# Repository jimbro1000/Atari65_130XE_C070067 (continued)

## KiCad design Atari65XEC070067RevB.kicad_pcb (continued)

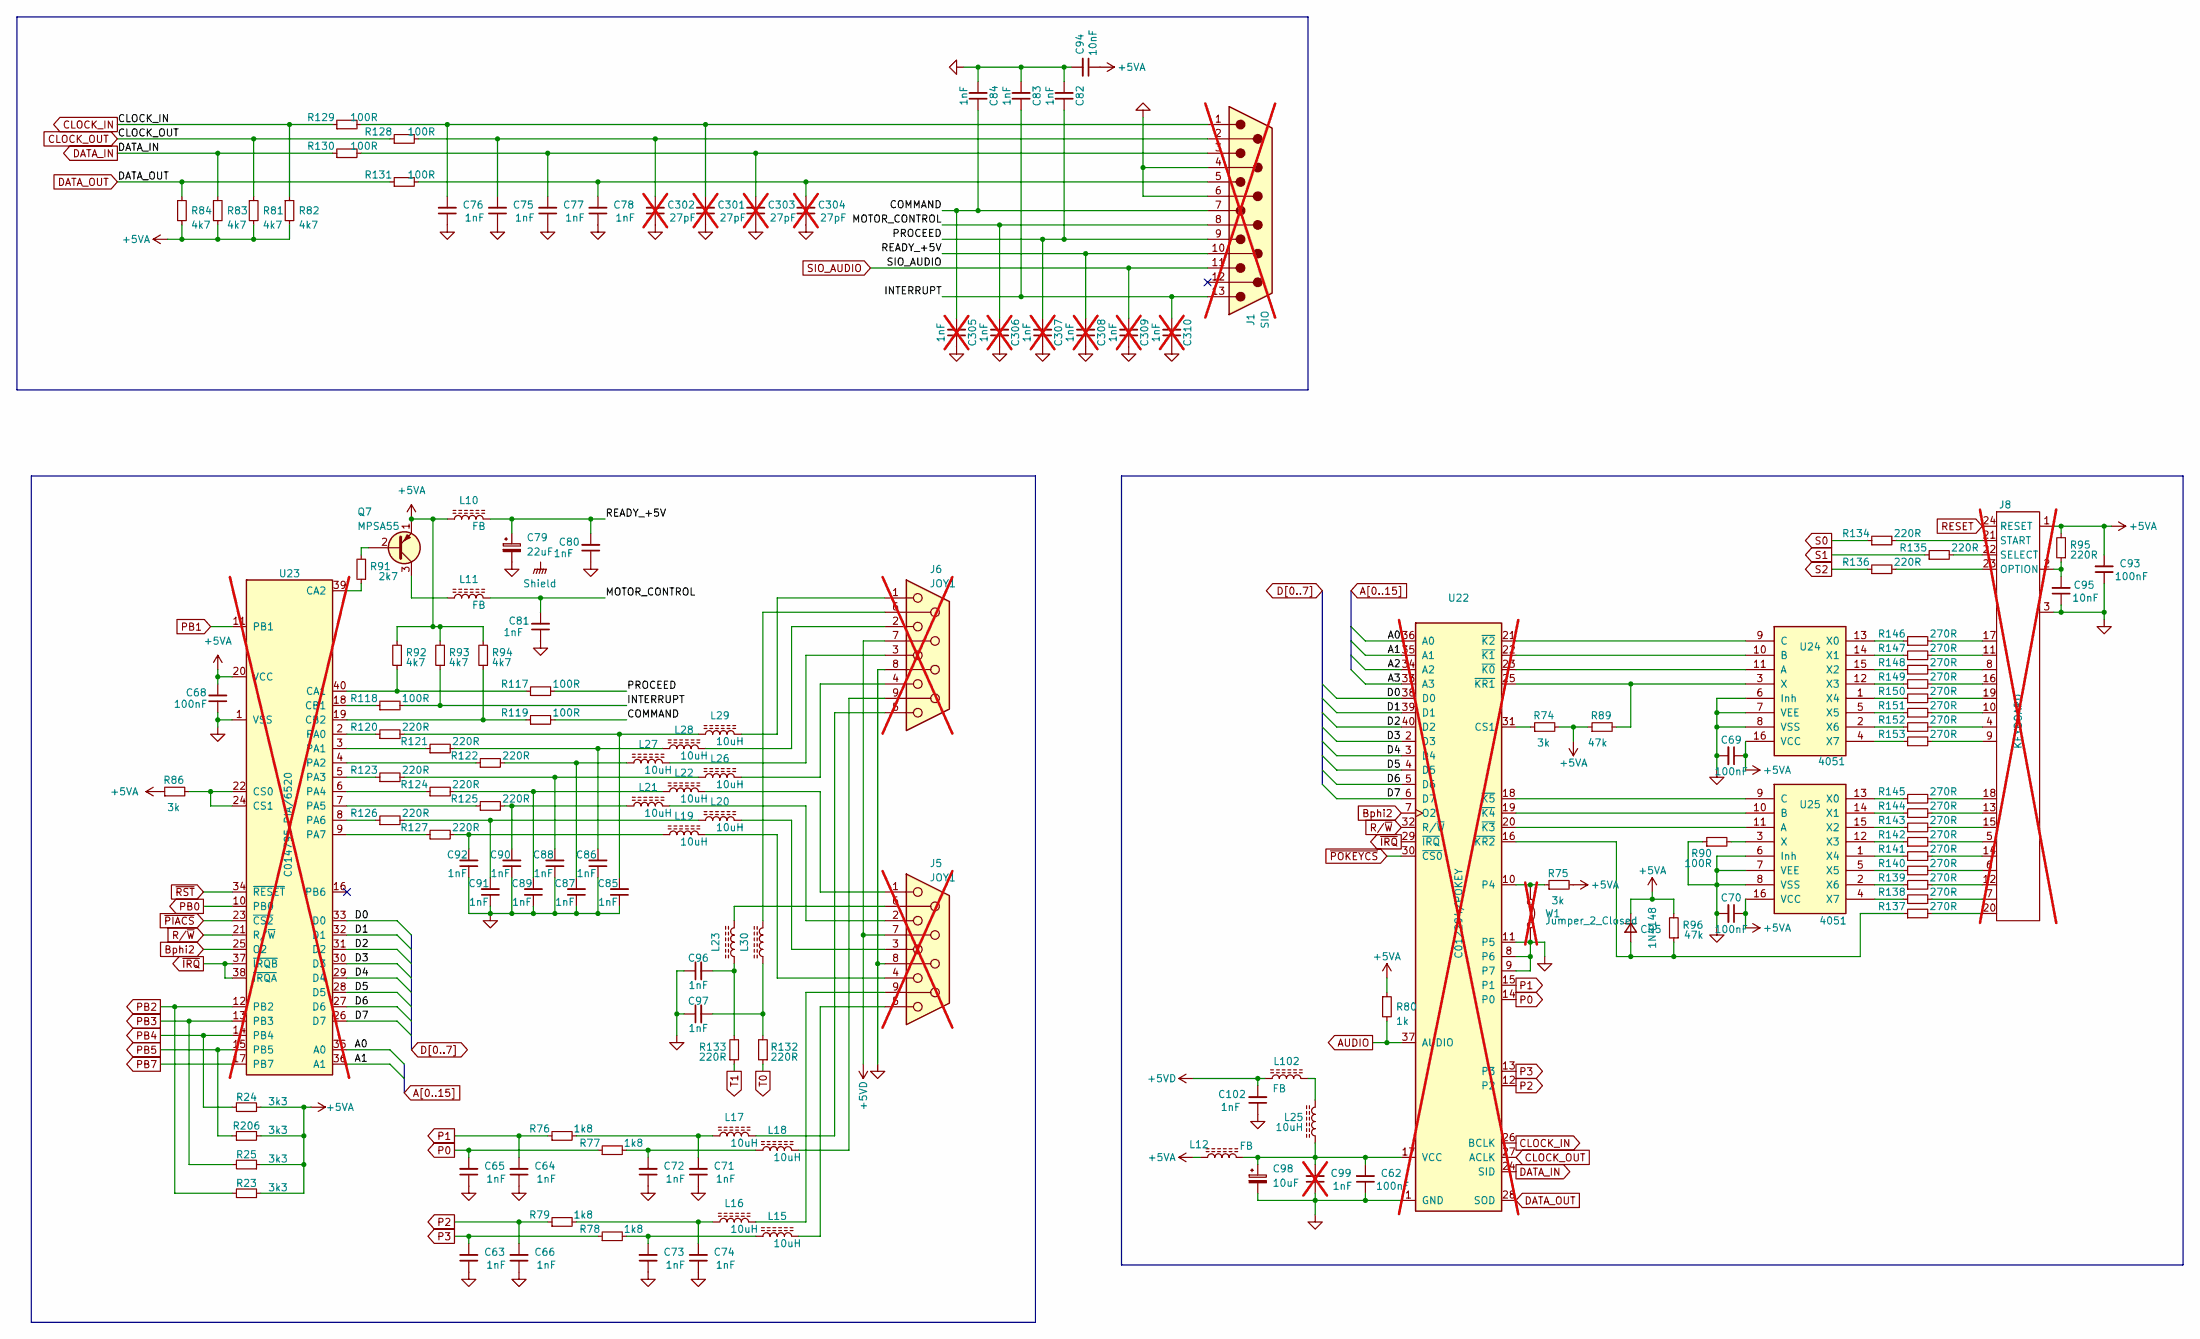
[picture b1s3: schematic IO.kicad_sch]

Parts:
C62, C68, C69, C70, C93: 100nF; C_Axial_L5.1mm_D2.7mm_P12.72mm_Horizontal; DigiKey 1109PHCT-ND
C63, C64, C65, C66, C71, C72, C73, C74, C75, C76, C77, C78, C80, C81, C82, C83, C84, C85, C86, C87, C88, C89, C90, C91, C92, C96, C97, C102: 1nF; C_Axial_L5.1mm_D2.7mm_P12.72mm_Horizontal; DigiKey 1216PHCT-ND
C79: 22uF; CP_Axial_L11.0mm_D5.0mm_P18.00mm_Horizontal; DigiKey 1572-1393-ND
C94, C95: 10nF; C_Axial_L5.1mm_D2.7mm_P12.72mm_Horizontal; DigiKey 1103PHCT-ND
C98: 10uF; CP_Axial_L11.0mm_D5.0mm_P18.00mm_Horizontal; DigiKey 1572-1035-1-ND
C99: 1nF; C_Axial_L5.1mm_D2.7mm_P12.72mm_Horizontal; DigiKey 1216PHCT-ND; not fitted
C301, C302, C303, C304: 27pF; C_Disc_D3.0mm_W1.6mm_P3.0mm; not fitted
C305, C306, C307, C308, C309, C310: 1nF; C_Disc_D3.0mm_W1.6mm_P3.0mm; not fitted
CR5: 1N4148; D_DO-35_SOD27_P12.70mm_Horizontal; DigiKey 1N4148FS-ND
J1: SIO; DSUB-13_Pins_Horizontal_P2.77x2.84mm_EdgePinOffset7.70mm_Ho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; not fitted
J5, J6: JOY1; DSUB-9_Pins_Horizontal_P2.77x2.54mm_Atari; not fitted
J8: KEYBOARD; not fitted
L10, L11, L12, L23, L30, L102: FB; L_Axial_L7.0mm_D3.3mm_P12.70mm_Horizontal_Fastron_MICC; DigiKey 1934-1417-1-ND
L15, L16, L17, L18, L19, L20, L21, L22, L25, L26, L27, L28, L29: 10uH; L_Axial_L7.0mm_D3.3mm_P12.70mm_Horizontal_Fastron_MICC; DigiKey 535-AICC-02-100K-TCT-ND
Q7: MPSA55; TO-92L_Inline_Wide; DigiKey PN2907ABUFS-ND
R23, R24, R25, R206: 3k3; R_Axial_L9.0mm_D2.7mm_P12.70mm_Horizontal; DigiKey CF14JT3K30CT-ND
R74, R75, R86: 3k; R_Axial_L9.0mm_D2.7mm_P12.70mm_Horizontal; DigiKey CF14JT3K00CT-ND
R76, R77, R78, R79: 1k8; R_Axial_L9.0mm_D2.7mm_P12.70mm_Horizontal; DigiKey CF14JT1K80CT-ND
R80: 1k; R_Axial_L9.0mm_D2.7mm_P12.70mm_Horizontal; DigiKey CF14JT1K00CT-ND
R81, R82, R83, R84, R92, R93, R94: 4k7; R_Axial_L9.0mm_D2.7mm_P12.70mm_Horizontal; DigiKey CF14JT4K70CT-ND
R89, R96: 47k; R_Axial_L9.0mm_D2.7mm_P12.70mm_Horizontal; DigiKey S47KQCT-ND
R90, R117, R118, R119, R128, R129, R130, R131: 100R; R_Axial_L9.0mm_D2.7mm_P12.70mm_Horizontal; DigiKey CF14JT100RCT-ND
R91: 2k7; R_Axial_L9.0mm_D2.7mm_P12.70mm_Horizontal; DigiKey CF14JT2K70CT-ND
R95, R120, R121, R122, R123, R124, R125, R126, R127, R132, R133, R134, R135, R136: 220R; R_Axial_L9.0mm_D2.7mm_P12.70mm_Horizontal; DigiKey CF14JT220RCT-ND
R137, R138, R139, R140, R141, R142, R143, R144, R145, R146, R147, R148, R149, R150, R151, R152, R153: 270R; R_Axial_L9.0mm_D2.7mm_P12.70mm_Horizontal; DigiKey CF14JT270RCT-ND
U22: C012294/POKEY; DIP-40_W15.24mm; not fitted
U23: C014795 PIA/6520; DIP-40_W15.24mm; not fitted
U24, U25: 4051; DIP-16_W7.62mm; DigiKey 296-2057-5-ND
W1: Jumper_2_Closed; R_Axial_DIN0309_L9.0mm_D3.2mm_P12.70mm_Horizontal; not fitted

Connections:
+5VA: C68.2, C69.1, C70.1, C93.2, C94.1, CR5.1 (K), J8.1, L10.1, L12.1, Q7.1 (E), R23.1, R24.1, R25.1, R74.2, R75.2, R80.1, R81.2, R82.2, R83.2, R84.2, R86.1, R89.1, R92.2, R93.2, R94.2, R95.2, R96.2, R206.2, U23.20 (VCC), U24.16 (VCC), U25.16 (VCC); also elsewhere on the board
+5VD: C102.2, J5.7, J6.7, L102.1
/IO/COMMAND: C84.1, C305.2, J1.7, R119.2
/IO/INTERRUPT: C83.1, C310.2, J1.13, R93.1, R118.2
/IO/MOTOR_CONTROL: C81.2, C306.2, J1.8, L11.2
/IO/PROCEED: C82.1, C307.2, J1.9, R117.2
/IO/READY_+5V: C79.1, C80.2, C308.2, J1.10, L10.2
A0: U22.36 (A0), U23.35 (A0); also elsewhere on the board
A1: U22.35 (A1), U23.36 (A1); also elsewhere on the board
A2: U22.34 (A2); also elsewhere on the board
A3: U22.33 (A3); also elsewhere on the board
AUDIO: R80.2, U22.37 (AUDIO); also elsewhere on the board
Bphi2: U22.7 (O2), U23.25 (O2); also elsewhere on the board
CLOCK_IN: R82.1, R129.1, U22.26 (BCLK)
CLOCK_OUT: R81.1, R128.1, U22.27 (ACLK)
D0: U22.38 (D0), U23.33 (D0); also elsewhere on the board
D1: U22.39 (D1), U23.32 (D1); also elsewhere on the board
D2: U22.40 (D2), U23.31 (D2); also elsewhere on the board
D3: U22.2 (D3), U23.30 (D3); also elsewhere on the board
D4: U22.3 (D4), U23.29 (D4); also elsewhere on the board
D5: U22.4 (D5), U23.28 (D5); also elsewhere on the board
D6: U22.5 (D6), U23.27 (D6); also elsewhere on the board
D7: U22.6 (D7), U23.26 (D7); also elsewhere on the board
DATA_IN: R83.1, R130.1, U22.24 (SID)
DATA_OUT: R84.1, R131.1, U22.28 (SOD)
GND: C62.1, C63.1, C64.1, C65.1, C66.1, C68.1, C69.2, C70.2, C71.1, C72.1, C73.1, C74.1, C75.1, C76.1, C77.1, C78.1, C79.2, C80.1, C81.1, C82.2, C83.2, C84.2, C85.1, C86.1, C87.1, C88.1, C89.1, C90.1, C91.1, C92.1, C93.1, C94.2, C95.1, C96.1, C97.1, C98.2, C99.1, C102.1, C301.1, C302.1, C303.1, C304.1, C305.1, C306.1, C307.1, C308.1, C309.1, C310.1, J1.4, J1.6, J5.8, J6.8, J8.3, R90.1, U22.1 (GND), U22.8 (P6), U22.9 (P7), U22.11 (P5), U23.1 (VSS), U24.6 (Inh), U24.7 (VEE), U24.8 (VSS), U25.6 (Inh), U25.7 (VEE), U25.8 (VSS), W1.2 (B); also elsewhere on the board
unnamed: C71.2, L17.1, R76.2
unnamed: C72.2, L18.1, R77.2
unnamed: C73.2, L15.1, R78.2
unnamed: C74.2, L16.1, R79.2
unnamed: C85.2, L29.1, R120.2
unnamed: C86.2, L28.1, R121.2
unnamed: C87.2, L27.1, R122.2
unnamed: C88.2, L26.1, R123.2
unnamed: C89.2, L22.1, R124.2
unnamed: C90.2, L21.1, R125.2
unnamed: C91.2, L20.1, R126.2
unnamed: C92.2, L19.1, R127.2
unnamed: C95.2, J8.2, R95.1
unnamed: C96.2, L23.1, R133.2
unnamed: C97.2, L30.1, R132.2
unnamed: C76.2, C301.2, J1.1, R129.2
unnamed: C75.2, C302.2, J1.2, R128.2
unnamed: C77.2, C303.2, J1.3, R130.2
unnamed: C78.2, C304.2, J1.5, R131.2
unnamed: CR5.2 (A), R96.1, R137.1, U22.16 (~KR2)
unnamed: J5.1, L22.2
unnamed: J5.2, L21.2
unnamed: J5.3, L20.2
unnamed: J5.4, L19.2
unnamed: J5.5, L15.2
unnamed: J5.6, L23.2
unnamed: J5.9, L16.2
unnamed: J6.1, L29.2
unnamed: J6.2, L28.2
unnamed: J6.3, L27.2
unnamed: J6.4, L26.2
unnamed: J6.5, L17.2
unnamed: J6.6, L30.2
unnamed: J6.9, L18.2
unnamed: J8.23 (OPTION), R136.2
unnamed: J8.4, R152.2
unnamed: J8.5, R142.2
unnamed: J8.6, R140.2
unnamed: J8.7, R138.2
unnamed: J8.8, R148.2
unnamed: J8.9, R153.2
unnamed: J8.10, R151.2
unnamed: J8.11, R147.2
unnamed: J8.12, R139.2
unnamed: J8.13, R144.2
unnamed: J8.14, R141.2
unnamed: J8.15, R143.2
unnamed: J8.16, R149.2
unnamed: J8.17, R146.2
unnamed: J8.18, R145.2
unnamed: J8.19, R150.2
unnamed: J8.20, R137.2
unnamed: J8.22 (SELECT), R135.2
unnamed: J8.21 (START), R134.2
unnamed: L25.2, L102.2
unnamed: Q7.2 (B), R91.2
unnamed: L11.1, Q7.3 (C)
unnamed: R74.1, U22.31 (CS1)
unnamed: R75.1, U22.10 (P4), W1.1 (A)
unnamed: C62.2, C98.1, C99.2, L12.2, L25.1, U22.17 (VCC)
unnamed: U22.23 (~K0), U24.11 (A)
unnamed: U22.22 (~K1), U24.10 (B)
unnamed: U22.21 (~K2), U24.9 (C)
unnamed: U22.20 (~K3), U25.11 (A)
unnamed: U22.19 (~K4), U25.10 (B)
unnamed: U22.18 (~K5), U25.9 (C)
unnamed: R89.2, U22.25 (~KR1), U24.3 (X)
unnamed: R92.1, R117.1, U23.40 (CA1)
unnamed: R91.1, U23.39 (CA2)
unnamed: R118.1, U23.18 (CB1)
unnamed: R94.1, R119.1, U23.19 (CB2)
unnamed: R86.2, U23.22 (CS0), U23.24 (CS1)
unnamed: R120.1, U23.2 (PA0)
unnamed: R121.1, U23.3 (PA1)
unnamed: R122.1, U23.4 (PA2)
unnamed: R123.1, U23.5 (PA3)
unnamed: R124.1, U23.6 (PA4)
unnamed: R125.1, U23.7 (PA5)
unnamed: R126.1, U23.8 (PA6)
unnamed: R127.1, U23.9 (PA7)
unnamed: R146.1, U24.13 (X0)
unnamed: R147.1, U24.14 (X1)
unnamed: R148.1, U24.15 (X2)
unnamed: R149.1, U24.12 (X3)
unnamed: R150.1, U24.1 (X4)
unnamed: R151.1, U24.5 (X5)
unnamed: R152.1, U24.2 (X6)
unnamed: R153.1, U24.4 (X7)
unnamed: R145.1, U25.13 (X0)
unnamed: R144.1, U25.14 (X1)
unnamed: R143.1, U25.15 (X2)
unnamed: R142.1, U25.12 (X3)
unnamed: R141.1, U25.1 (X4)
unnamed: R140.1, U25.5 (X5)
unnamed: R139.1, U25.2 (X6)
unnamed: R138.1, U25.4 (X7)
unnamed: R90.2, U25.3 (X)
P0: C65.2, R77.1, U22.14 (P0)
P1: C64.2, R76.1, U22.15 (P1)
P2: C66.2, R79.1, U22.12 (P2)
P3: C63.2, R78.1, U22.13 (P3)
PB0: U23.10 (PB0); also elsewhere on the board
PB1: U23.11 (PB1); also elsewhere on the board
PB2: R23.2, U23.12 (PB2); also elsewhere on the board
PB3: R25.2, U23.13 (PB3); also elsewhere on the board
PB4: R24.2, U23.14 (PB4); also elsewhere on the board
PB5: R206.1, U23.15 (PB5); also elsewhere on the board
PB7: U23.17 (PB7); also elsewhere on the board
RESET: J8.24 (RESET); also elsewhere on the board
R/~W: U22.32 (R/~W), U23.21 (R/~W); also elsewhere on the board
S0: R134.1; also elsewhere on the board
S1: R135.1; also elsewhere on the board
S2: R136.1; also elsewhere on the board
SIO_AUDIO: C309.2, J1.11; also elsewhere on the board
T0: R132.1; also elsewhere on the board
T1: R133.1; also elsewhere on the board
~IRQ: U22.29 (~IRQ), U23.37 (~IRQB), U23.38 (~IRQA); also elsewhere on the board
~PIACS: U23.23 (~CS2); also elsewhere on the board
~POKEYCS: U22.30 (~CS0); also elsewhere on the board
~RST: U23.34 (~RESET); also elsewhere on the board

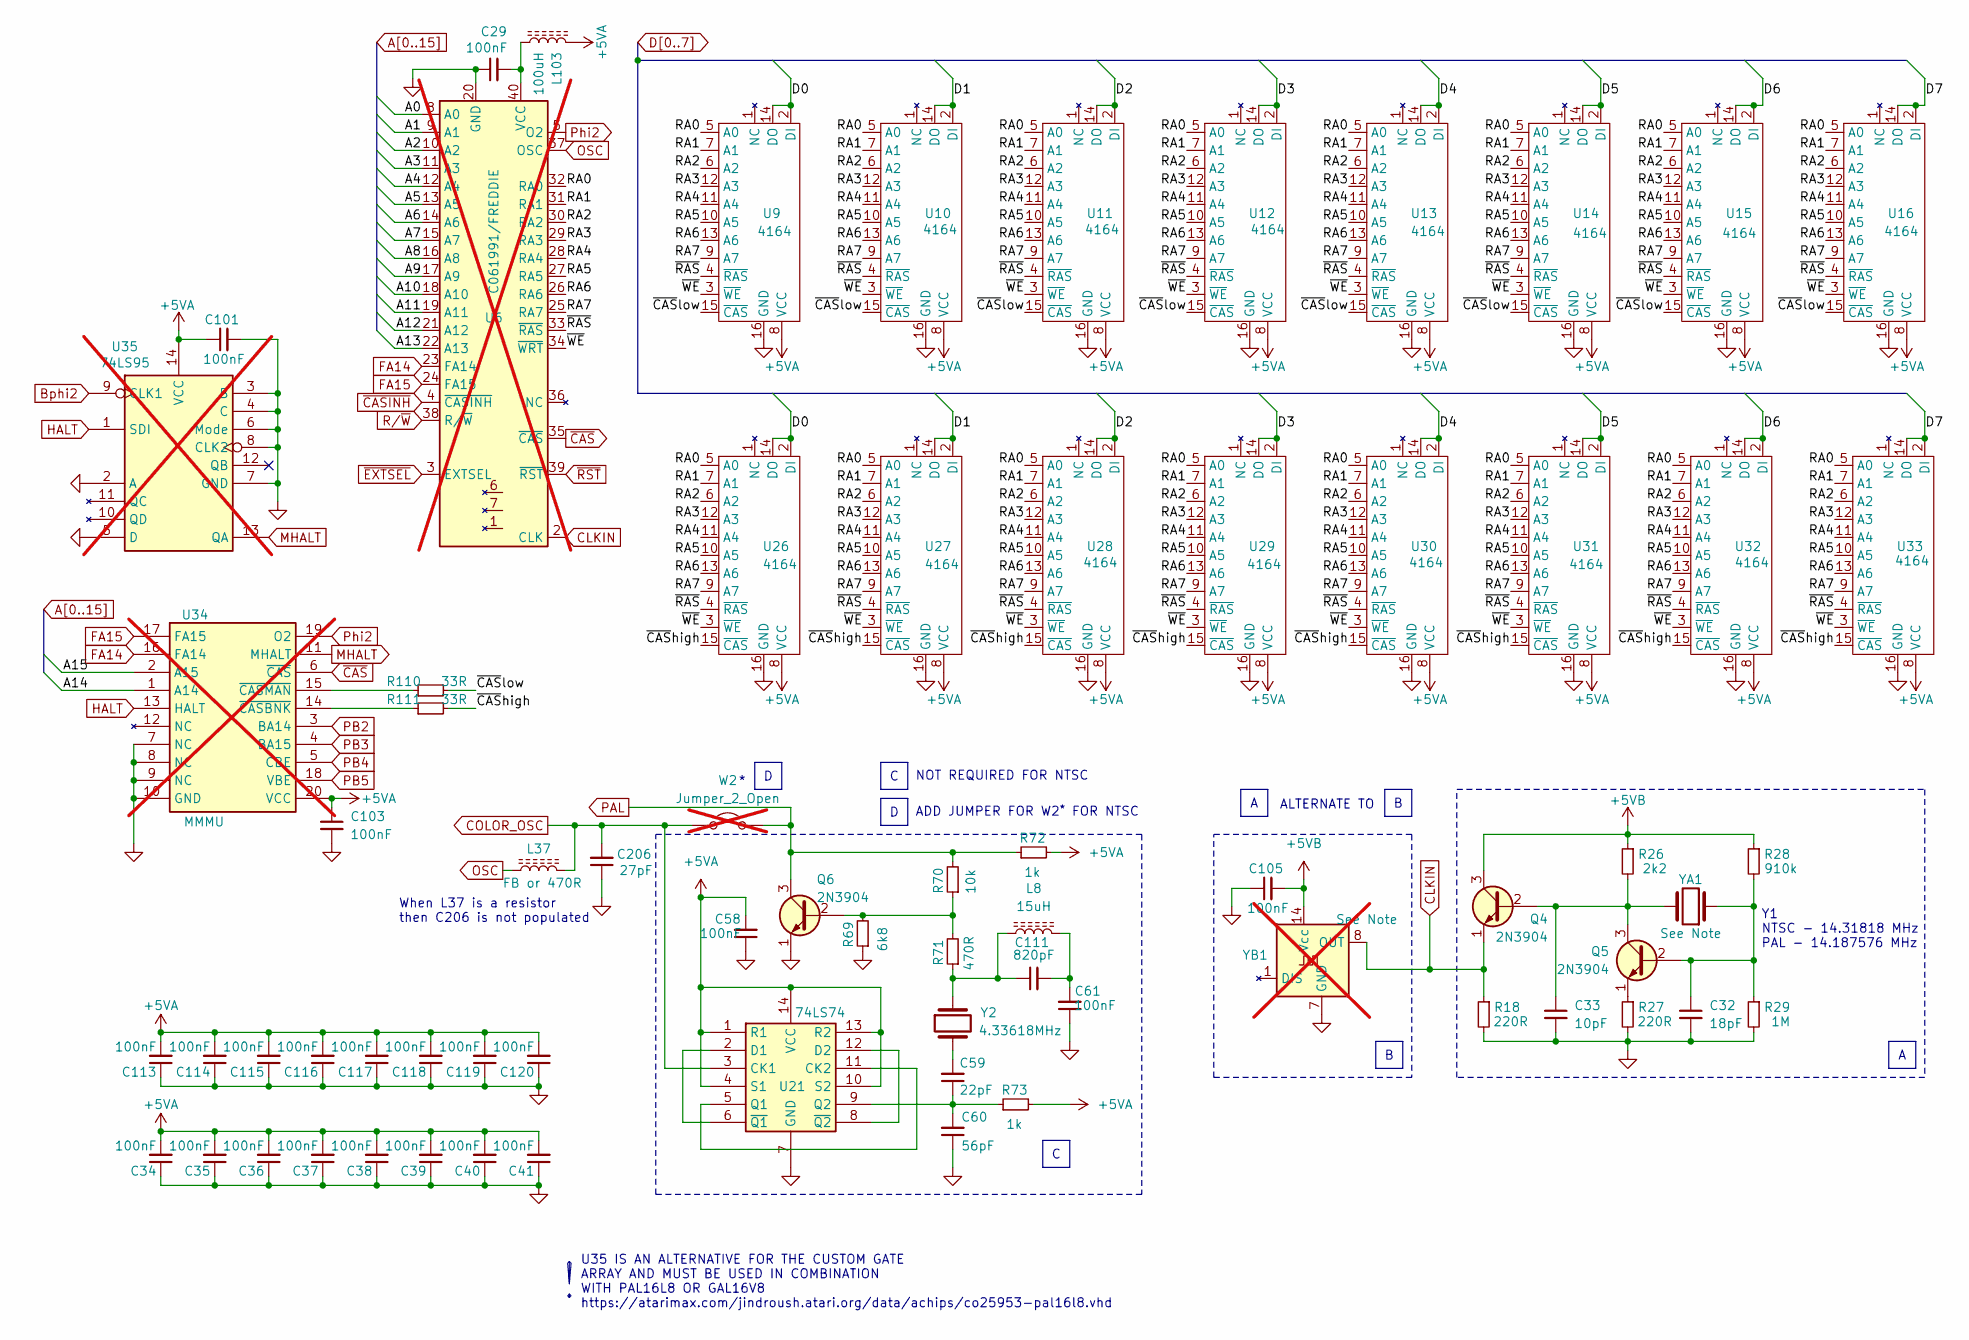
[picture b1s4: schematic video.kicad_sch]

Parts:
C29, C58, C61, C101, C103, C105: 100nF; C_Axial_L5.1mm_D2.7mm_P12.72mm_Horizontal; DigiKey 1109PHCT-ND
C32: 18pF; C_Axial_L5.1mm_D2.7mm_P12.72mm_Horizontal; DigiKey 1013PHCT-ND
C33: 10pF; C_Axial_L5.1mm_D2.7mm_P12.72mm_Horizontal; DigiKey 1011PHCT-ND
C34, C35, C36, C37, C38, C39, C40, C41, C113, C114, C115, C116, C117, C118, C119, C120: 100nF; C_Axial_L3.8mm_D2.6mm_P8.89mm_Horizontal; DigiKey 1109PHCT-ND
C59: 22pF; C_Axial_L5.1mm_D2.7mm_P12.72mm_Horizontal; DigiKey 1014PHCT-ND
C60: 56pF; C_Axial_L5.1mm_D2.7mm_P12.72mm_Horizontal; DigiKey 399-C410C510FAG5TA-ND
C111: 820pF; C_Axial_L5.1mm_D2.7mm_P12.72mm_Horizontal; DigiKey 399-C410C821K1R5TA-ND
C206: 27pF; C_Axial_L5.1mm_D2.7mm_P12.72mm_Horizontal; DigiKey 1015PHCT-ND
L8: 15uH; R_Axial_L9.0mm_D2.7mm_P12.70mm_Horizontal; DigiKey 78F150J-RC-ND
L37: FB or 470R; R_Axial_L9.0mm_D2.7mm_P12.70mm_Horizontal; DigiKey 1934-1417-1-ND
L103: 100uH; L_Axial_L7.0mm_D3.3mm_P12.70mm_Horizontal_Fastron_MICC; DigiKey 118-78F101J-TR-RCCT-ND
Q4, Q5, Q6: 2N3904; TO-92L_Inline_Wide; DigiKey 4878-2N3904CT-ND
R18, R27: 220R; R_Axial_L9.0mm_D2.7mm_P12.70mm_Horizontal; DigiKey CF14JT220RCT-ND
R26: 2k2; R_Axial_L9.0mm_D2.7mm_P12.70mm_Horizontal; DigiKey CF14JT2K20CT-ND
R28: 910k; R_Axial_L9.0mm_D2.7mm_P12.70mm_Horizontal; DigiKey CF14JT910KCT-ND
R29: 1M; R_Axial_L9.0mm_D2.7mm_P12.70mm_Horizontal; DigiKey CF14JT1M00CT-ND
R69: 6k8; R_Axial_L9.0mm_D2.7mm_P12.70mm_Horizontal; DigiKey CF14JT6K80CT-ND
R70: 10k; R_Axial_L9.0mm_D2.7mm_P12.70mm_Horizontal; DigiKey CF14JT10K0CT-ND
R71: 470R; R_Axial_L9.0mm_D2.7mm_P12.70mm_Horizontal; DigiKey CF14JT470RCT-ND
R72, R73: 1k; R_Axial_L9.0mm_D2.7mm_P12.70mm_Horizontal; DigiKey CF14JT1K00CT-ND
R110, R111: 33R; R_Axial_L9.0mm_D2.7mm_P12.70mm_Horizontal; DigiKey CF14JT33R0CT-ND
U6: C061991/FREDDIE; DIP-40_W15.24mm; not fitted
U9, U10, U11, U12, U13, U14, U15, U16, U26, U27, U28, U29, U30, U31, U32, U33: 4164; DIP-16_W7.62mm
U21: 74LS74; DIP-14_W7.62mm; DigiKey 296-1668-5-ND
U34: MMMU; DIP-20_W7.62mm; not fitted
U35: 74LS95; DIP-14_W7.62mm; not fitted
W2: Jumper_2_Open; R_Axial_DIN0309_L9.0mm_D3.2mm_P12.70mm_Horizontal; not fitted
Y2: 4.33618MHz; Crystal_HC49-U_Horizontal; DigiKey X1013-ND
YA1: See Note; Crystal_HC49-U_Horizontal; DigiKey 535-AB-14.31818MHZ-B2CT-ND
YB1: See Note; Oscillator_DIP-14; DigiKey X946-ND; not fitted

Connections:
+5VA: C34.2, C35.2, C36.2, C37.2, C38.2, C39.2, C40.2, C41.2, C58.2, C101.1, C103.1, C113.2, C114.2, C115.2, C116.2, C117.2, C118.2, C119.2, C120.2, L103.2, R72.2, R73.2, U9.8 (VCC), U10.8 (VCC), U11.8 (VCC), U12.8 (VCC), U13.8 (VCC), U14.8 (VCC), U15.8 (VCC), U16.8 (VCC), U21.1 (R1), U21.4 (S1), U21.10 (S2), U21.13 (R2), U21.14 (VCC), U26.8 (VCC), U27.8 (VCC), U28.8 (VCC), U29.8 (VCC), U30.8 (VCC), U31.8 (VCC), U32.8 (VCC), U33.8 (VCC), U34.20 (VCC), U35.14 (VCC); also elsewhere on the board
+5VB: C105.2, Q4.3 (C), R26.1, R28.1, YB1.14 (Vcc); also elsewhere on the board
/clocks+ram/RA0: U6.32 (RA0), U9.5 (A0), U10.5 (A0), U11.5 (A0), U12.5 (A0), U13.5 (A0), U14.5 (A0), U15.5 (A0), U16.5 (A0), U26.5 (A0), U27.5 (A0), U28.5 (A0), U29.5 (A0), U30.5 (A0), U31.5 (A0), U32.5 (A0), U33.5 (A0)
/clocks+ram/RA1: U6.31 (RA1), U9.7 (A1), U10.7 (A1), U11.7 (A1), U12.7 (A1), U13.7 (A1), U14.7 (A1), U15.7 (A1), U16.7 (A1), U26.7 (A1), U27.7 (A1), U28.7 (A1), U29.7 (A1), U30.7 (A1), U31.7 (A1), U32.7 (A1), U33.7 (A1)
/clocks+ram/RA2: U6.30 (RA2), U9.6 (A2), U10.6 (A2), U11.6 (A2), U12.6 (A2), U13.6 (A2), U14.6 (A2), U15.6 (A2), U16.6 (A2), U26.6 (A2), U27.6 (A2), U28.6 (A2), U29.6 (A2), U30.6 (A2), U31.6 (A2), U32.6 (A2), U33.6 (A2)
/clocks+ram/RA3: U6.29 (RA3), U9.12 (A3), U10.12 (A3), U11.12 (A3), U12.12 (A3), U13.12 (A3), U14.12 (A3), U15.12 (A3), U16.12 (A3), U26.12 (A3), U27.12 (A3), U28.12 (A3), U29.12 (A3), U30.12 (A3), U31.12 (A3), U32.12 (A3), U33.12 (A3)
/clocks+ram/RA4: U6.28 (RA4), U9.11 (A4), U10.11 (A4), U11.11 (A4), U12.11 (A4), U13.11 (A4), U14.11 (A4), U15.11 (A4), U16.11 (A4), U26.11 (A4), U27.11 (A4), U28.11 (A4), U29.11 (A4), U30.11 (A4), U31.11 (A4), U32.11 (A4), U33.11 (A4)
/clocks+ram/RA5: U6.27 (RA5), U9.10 (A5), U10.10 (A5), U11.10 (A5), U12.10 (A5), U13.10 (A5), U14.10 (A5), U15.10 (A5), U16.10 (A5), U26.10 (A5), U27.10 (A5), U28.10 (A5), U29.10 (A5), U30.10 (A5), U31.10 (A5), U32.10 (A5), U33.10 (A5)
/clocks+ram/RA6: U6.26 (RA6), U9.13 (A6), U10.13 (A6), U11.13 (A6), U12.13 (A6), U13.13 (A6), U14.13 (A6), U15.13 (A6), U16.13 (A6), U26.13 (A6), U27.13 (A6), U28.13 (A6), U29.13 (A6), U30.13 (A6), U31.13 (A6), U32.13 (A6), U33.13 (A6)
/clocks+ram/RA7: U6.25 (RA7), U9.9 (A7), U10.9 (A7), U11.9 (A7), U12.9 (A7), U13.9 (A7), U14.9 (A7), U15.9 (A7), U16.9 (A7), U26.9 (A7), U27.9 (A7), U28.9 (A7), U29.9 (A7), U30.9 (A7), U31.9 (A7), U32.9 (A7), U33.9 (A7)
/clocks+ram/~CAShigh: R111.2, U26.15 (~CAS), U27.15 (~CAS), U28.15 (~CAS), U29.15 (~CAS), U30.15 (~CAS), U31.15 (~CAS), U32.15 (~CAS), U33.15 (~CAS)
/clocks+ram/~CASlow: R110.2, U9.15 (~CAS), U10.15 (~CAS), U11.15 (~CAS), U12.15 (~CAS), U13.15 (~CAS), U14.15 (~CAS), U15.15 (~CAS), U16.15 (~CAS)
/clocks+ram/~RAS: U6.33 (~RAS), U9.4 (~RAS), U10.4 (~RAS), U11.4 (~RAS), U12.4 (~RAS), U13.4 (~RAS), U14.4 (~RAS), U15.4 (~RAS), U16.4 (~RAS), U26.4 (~RAS), U27.4 (~RAS), U28.4 (~RAS), U29.4 (~RAS), U30.4 (~RAS), U31.4 (~RAS), U32.4 (~RAS), U33.4 (~RAS)
/clocks+ram/~WE: U6.34 (~WRT), U9.3 (~WE), U10.3 (~WE), U11.3 (~WE), U12.3 (~WE), U13.3 (~WE), U14.3 (~WE), U15.3 (~WE), U16.3 (~WE), U26.3 (~WE), U27.3 (~WE), U28.3 (~WE), U29.3 (~WE), U30.3 (~WE), U31.3 (~WE), U32.3 (~WE), U33.3 (~WE)
A0: U6.8 (A0); also elsewhere on the board
A1: U6.9 (A1); also elsewhere on the board
A2: U6.10 (A2); also elsewhere on the board
A3: U6.11 (A3); also elsewhere on the board
A4: U6.12 (A4); also elsewhere on the board
A5: U6.13 (A5); also elsewhere on the board
A6: U6.14 (A6); also elsewhere on the board
A7: U6.15 (A7); also elsewhere on the board
A8: U6.16 (A8); also elsewhere on the board
A9: U6.17 (A9); also elsewhere on the board
A10: U6.18 (A10); also elsewhere on the board
A11: U6.19 (A11); also elsewhere on the board
A12: U6.21 (A12); also elsewhere on the board
A13: U6.22 (A13); also elsewhere on the board
A14: U34.1 (A14); also elsewhere on the board
A15: U34.2 (A15); also elsewhere on the board
Bphi2: U35.9 (CLK1); also elsewhere on the board
CLKIN: Q4.1 (E), R18.1, U6.2 (CLK), YB1.8 (OUT)
COLOR_OSC: C206.2, L37.2, U21.3 (CK1), W2.1 (A); also elsewhere on the board
D0: U9.2 (DI), U9.14 (DO), U26.2 (DI), U26.14 (DO); also elsewhere on the board
D1: U10.2 (DI), U10.14 (DO), U27.2 (DI), U27.14 (DO); also elsewhere on the board
D2: U11.2 (DI), U11.14 (DO), U28.2 (DI), U28.14 (DO); also elsewhere on the board
D3: U12.2 (DI), U12.14 (DO), U29.2 (DI), U29.14 (DO); also elsewhere on the board
D4: U13.2 (DI), U13.14 (DO), U30.2 (DI), U30.14 (DO); also elsewhere on the board
D5: U14.2 (DI), U14.14 (DO), U31.2 (DI), U31.14 (DO); also elsewhere on the board
D6: U15.2 (DI), U15.14 (DO), U32.2 (DI), U32.14 (DO); also elsewhere on the board
D7: U16.2 (DI), U16.14 (DO), U33.2 (DI), U33.14 (DO); also elsewhere on the board
FA14: U6.23 (FA14), U34.16 (FA14)
FA15: U6.24 (FA15), U34.17 (FA15)
GND: C29.1, C32.2, C33.2, C34.1, C35.1, C36.1, C37.1, C38.1, C39.1, C40.1, C41.1, C58.1, C60.1, C61.1, C101.2, C103.2, C105.1, C113.1, C114.1, C115.1, C116.1, C117.1, C118.1, C119.1, C120.1, C206.1, Q6.1 (E), R18.2, R27.2, R29.2, R69.1, U6.20 (GND), U9.16 (GND), U10.16 (GND), U11.16 (GND), U12.16 (GND), U13.16 (GND), U14.16 (GND), U15.16 (GND), U16.16 (GND), U21.7 (GND), U26.16 (GND), U27.16 (GND), U28.16 (GND), U29.16 (GND), U30.16 (GND), U31.16 (GND), U32.16 (GND), U33.16 (GND), U34.7 (NC), U34.8 (NC), U34.9 (NC), U34.10 (GND), U35.2 (A), U35.3 (B), U35.4 (C), U35.5 (D), U35.6 (Mode), U35.7 (GND), U35.8 (CLK2), YB1.7 (GND); also elsewhere on the board
HALT: U34.13 (HALT), U35.1 (SDI); also elsewhere on the board
MHALT: U34.11 (MHALT), U35.13 (QA)
unnamed: C59.2, Y2.2
unnamed: C111.1, L8.1, R71.1, Y2.1
unnamed: C61.2, C111.2, L8.2
unnamed: C33.1, Q4.2 (B), Q5.3 (C), R26.2, YA1.2
unnamed: C32.1, Q5.2 (B), R28.2, R29.1, YA1.1
unnamed: Q5.1 (E), R27.1
unnamed: Q6.2 (B), R69.2, R70.1, R71.2
unnamed: C29.2, L103.1, U6.40 (VCC)
unnamed: U21.5 (Q1), U21.11 (CK2)
unnamed: U21.2 (D1), U21.6 (~Q1)
unnamed: U21.8 (~Q2), U21.12 (D2)
unnamed: C59.1, C60.2, R73.1, U21.9 (Q2)
unnamed: R111.1, U34.14 (~CASBNK)
unnamed: R110.1, U34.15 (~CASMAN)
OSC: L37.1, U6.37 (OSC)
PAL: Q6.3 (C), R70.2, R72.1, W2.2 (B); also elsewhere on the board
PB2: U34.3 (BA14); also elsewhere on the board
PB3: U34.4 (BA15); also elsewhere on the board
PB4: U34.5 (CBE); also elsewhere on the board
PB5: U34.18 (VBE); also elsewhere on the board
Phi2: U6.5 (O2), U34.19 (O2); also elsewhere on the board
R/~W: U6.38 (R/~W); also elsewhere on the board
~CASINH: U6.4 (~CASINH); also elsewhere on the board
~CAS: U6.35 (~CAS), U34.6 (~CAS)
~EXTSEL: U6.3 (EXTSEL); also elsewhere on the board
~RST: U6.39 (~RST); also elsewhere on the board

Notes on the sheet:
U35 IS AN ALTERNATIVE FOR THE CUSTOM GATE ARRAY AND MUST BE USED IN COMBINATION WITH PAL16L8 OR GAL16V8 https://atarimax.com/jindroush.atari.org/data/achips/co25953-pal16l8.vhd
ADD JUMPER FOR W2^{*} FOR NTSC
NOT REQUIRED FOR NTSC
Y1 NTSC - 14.31818 MHz PAL - 14.187576 MHz
When L37 is a resistor then C206 is not populated
ALTERNATE TO

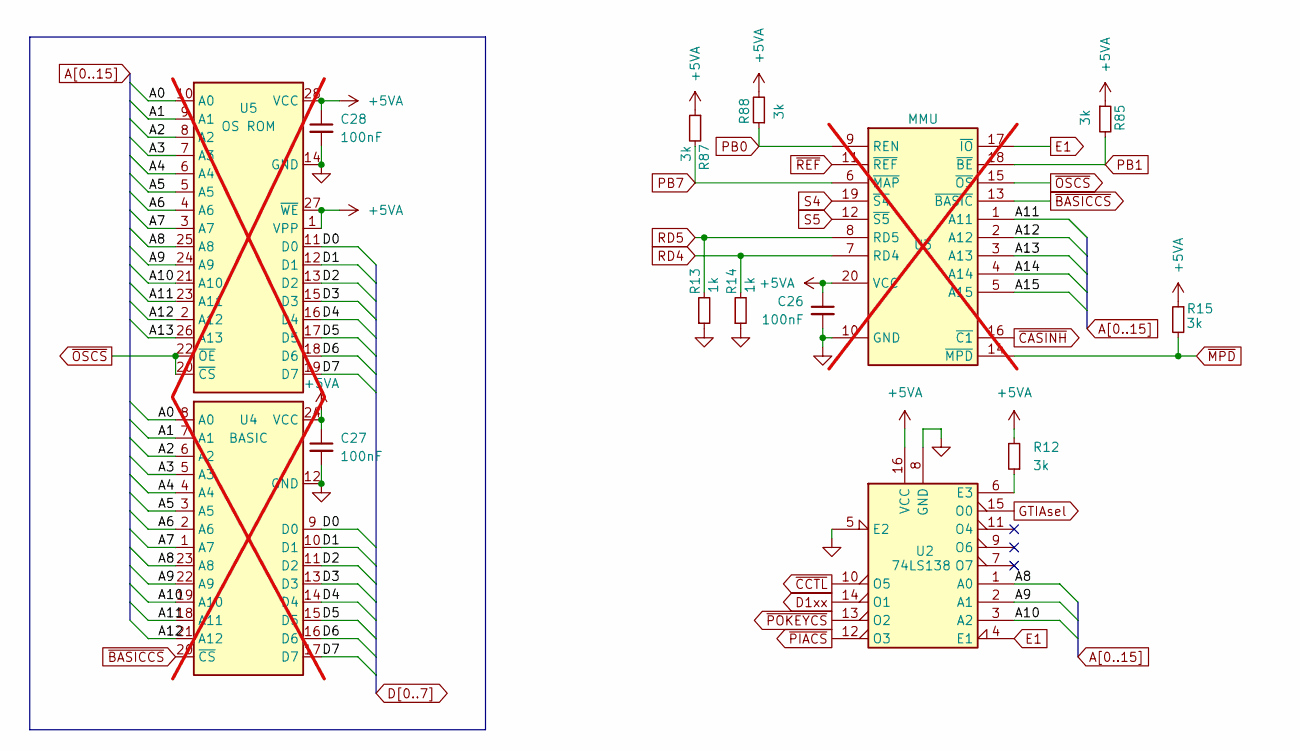
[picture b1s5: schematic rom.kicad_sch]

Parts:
C26, C27, C28: 100nF; C_Axial_L5.1mm_D2.7mm_P12.72mm_Horizontal; DigiKey 1109PHCT-ND
R12, R15, R85, R87, R88: 3k; R_Axial_L9.0mm_D2.7mm_P12.70mm_Horizontal; DigiKey CF14JT3K00CT-ND
R13, R14: 1k; R_Axial_L9.0mm_D2.7mm_P12.70mm_Horizontal; DigiKey CF14JT1K00CT-ND
U2: 74LS138; DIP-16_W7.62mm; DigiKey 296-1639-5-ND
U3: MMU; DIP-20_W7.62mm; not fitted
U4: BASIC; DIP-24_W15.24mm; not fitted
U5: OS ROM; DIP-28_W15.24mm; not fitted

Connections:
+5VA: C26.1, C27.1, C28.1, R12.2, R15.1, R85.1, R87.1, R88.2, U2.16 (VCC), U3.20 (VCC), U4.24 (VCC), U5.1 (VPP), U5.27 (~WE), U5.28 (VCC); also elsewhere on the board
A0: U4.8 (A0), U5.10 (A0); also elsewhere on the board
A1: U4.7 (A1), U5.9 (A1); also elsewhere on the board
A2: U4.6 (A2), U5.8 (A2); also elsewhere on the board
A3: U4.5 (A3), U5.7 (A3); also elsewhere on the board
A4: U4.4 (A4), U5.6 (A4); also elsewhere on the board
A5: U4.3 (A5), U5.5 (A5); also elsewhere on the board
A6: U4.2 (A6), U5.4 (A6); also elsewhere on the board
A7: U4.1 (A7), U5.3 (A7); also elsewhere on the board
A8: U2.1 (A0), U4.23 (A8), U5.25 (A8); also elsewhere on the board
A9: U2.2 (A1), U4.22 (A9), U5.24 (A9); also elsewhere on the board
A10: U2.3 (A2), U4.19 (A10), U5.21 (A10); also elsewhere on the board
A11: U3.1 (A11), U4.18 (A11), U5.23 (A11); also elsewhere on the board
A12: U3.2 (A12), U4.21 (A12), U5.2 (A12); also elsewhere on the board
A13: U3.3 (A13), U5.26 (A13); also elsewhere on the board
A14: U3.4 (A14); also elsewhere on the board
A15: U3.5 (A15); also elsewhere on the board
D0: U4.9 (D0), U5.11 (D0); also elsewhere on the board
D1: U4.10 (D1), U5.12 (D1); also elsewhere on the board
D1xx: U2.14 (O1); also elsewhere on the board
D2: U4.11 (D2), U5.13 (D2); also elsewhere on the board
D3: U4.13 (D3), U5.15 (D3); also elsewhere on the board
D4: U4.14 (D4), U5.16 (D4); also elsewhere on the board
D5: U4.15 (D5), U5.17 (D5); also elsewhere on the board
D6: U4.16 (D6), U5.18 (D6); also elsewhere on the board
D7: U4.17 (D7), U5.19 (D7); also elsewhere on the board
E1: U2.4 (E1), U3.17 (~IO)
GND: C26.2, C27.2, C28.2, R13.1, R14.1, U2.5 (E2), U2.8 (GND), U3.10 (GND), U4.12 (GND), U5.14 (GND); also elsewhere on the board
GTIAsel: U2.15 (O0); also elsewhere on the board
unnamed: R12.1, U2.6 (E3)
PB0: R88.1, U3.9 (REN); also elsewhere on the board
PB1: R85.2, U3.18 (~BE); also elsewhere on the board
PB7: R87.2, U3.6 (~MAP); also elsewhere on the board
RD4: R14.2, U3.7 (RD4); also elsewhere on the board
RD5: R13.2, U3.8 (RD5); also elsewhere on the board
S4: U3.19 (~S4); also elsewhere on the board
S5: U3.12 (~S5); also elsewhere on the board
~BASICCS: U3.13 (~BASIC), U4.20 (~CS)
~CASINH: U3.16 (~C1); also elsewhere on the board
~CCTL: U2.10 (O5); also elsewhere on the board
~MPD: R15.2, U3.14 (~MPD); also elsewhere on the board
~OSCS: U3.15 (~OS), U5.20 (~CS), U5.22 (~OE)
~PIACS: U2.12 (O3); also elsewhere on the board
~POKEYCS: U2.13 (O2); also elsewhere on the board
~REF: U3.11 (~REF); also elsewhere on the board

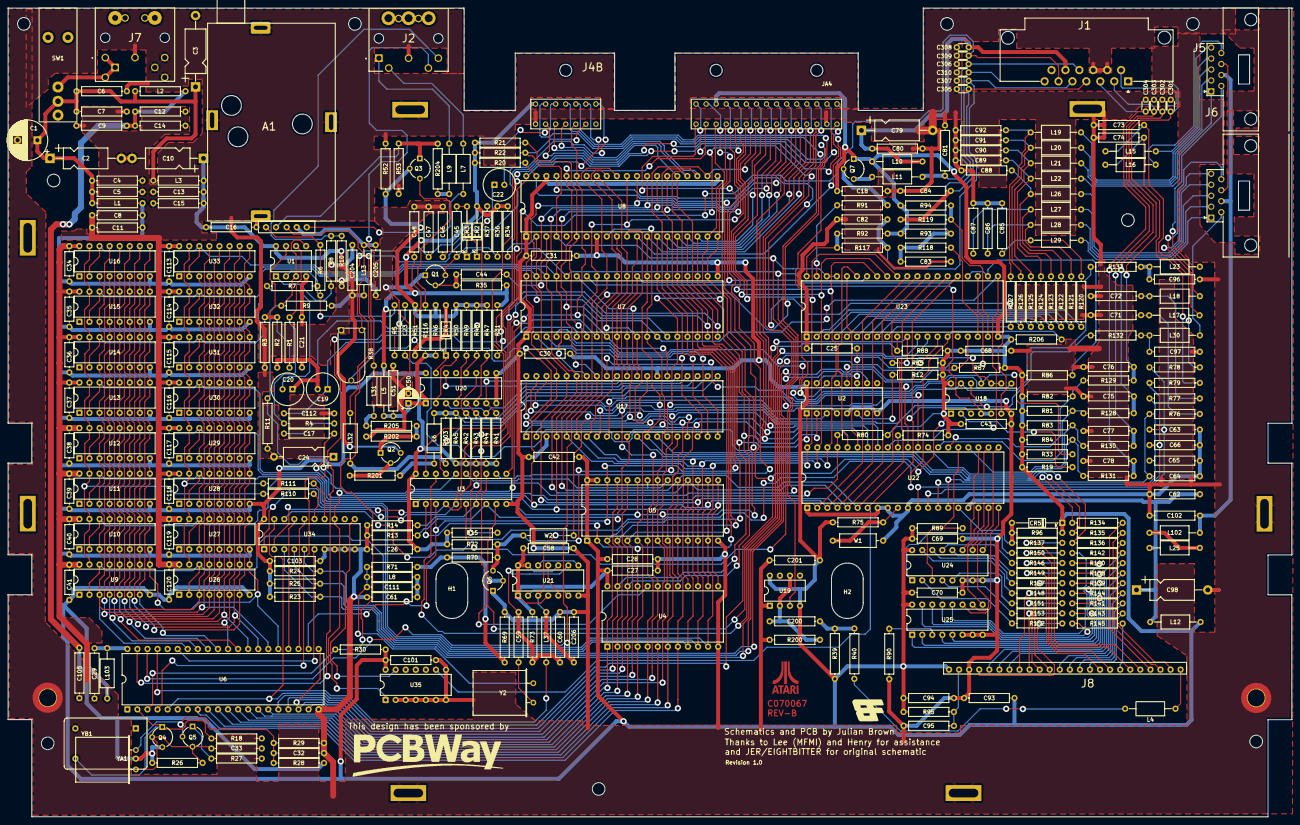
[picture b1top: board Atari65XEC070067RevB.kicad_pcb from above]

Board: 2 copper layers, 323.9 x 204.0 mm, 358 parts (0 on the bottom side), 275 nets.

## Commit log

2025-06-19 add ports
2025-06-20 complete schematic
2025-06-20 start layout
2025-06-20 initial pcb layout
2025-06-21 locate dram and trace around it
2025-06-21 progress routing
2025-06-22 update progress
2025-06-22 correct wiring of control keys to GTIA
2025-06-23 fix ROM positions
2025-06-24 fix phi2 wiring
2025-06-24 update pcb render
2025-06-26 update fills and footprints
2025-06-26 refine board definition
2025-06-27 place power circuit components
2025-06-27 fix lost work
2025-06-27 revise ram chip positions
2025-06-27 complete relocation of ram area
2025-06-29 update u35 and u34 schematic and routing
2025-06-30 fix design check errors
2025-06-30 progress routing, add modulator
2025-07-01 more routing
2025-07-06 fix din ports
2025-07-06 add sio port
2025-07-07 fix numbering for U6 and U8 (swapped), more routing
2025-07-07 finish component placing
2025-07-07 refine rf modulator footprint
2025-07-07 update readme and render
2025-07-11 progress routing, update README, add branding
2025-07-14 refine footprints
2025-07-14 rectify board dimensions
2025-07-15 fix SIO footprint and placement
2025-07-15 set mounting points
2025-07-17 complete revision 1
2025-07-24 provide component part nubmers for digikey
2025-07-25 provide BOM for digikey
2025-09-25 tidy up schematic
2025-09-28 tidy up
2025-09-29 tidy up video
2025-09-29 complete tidy up
